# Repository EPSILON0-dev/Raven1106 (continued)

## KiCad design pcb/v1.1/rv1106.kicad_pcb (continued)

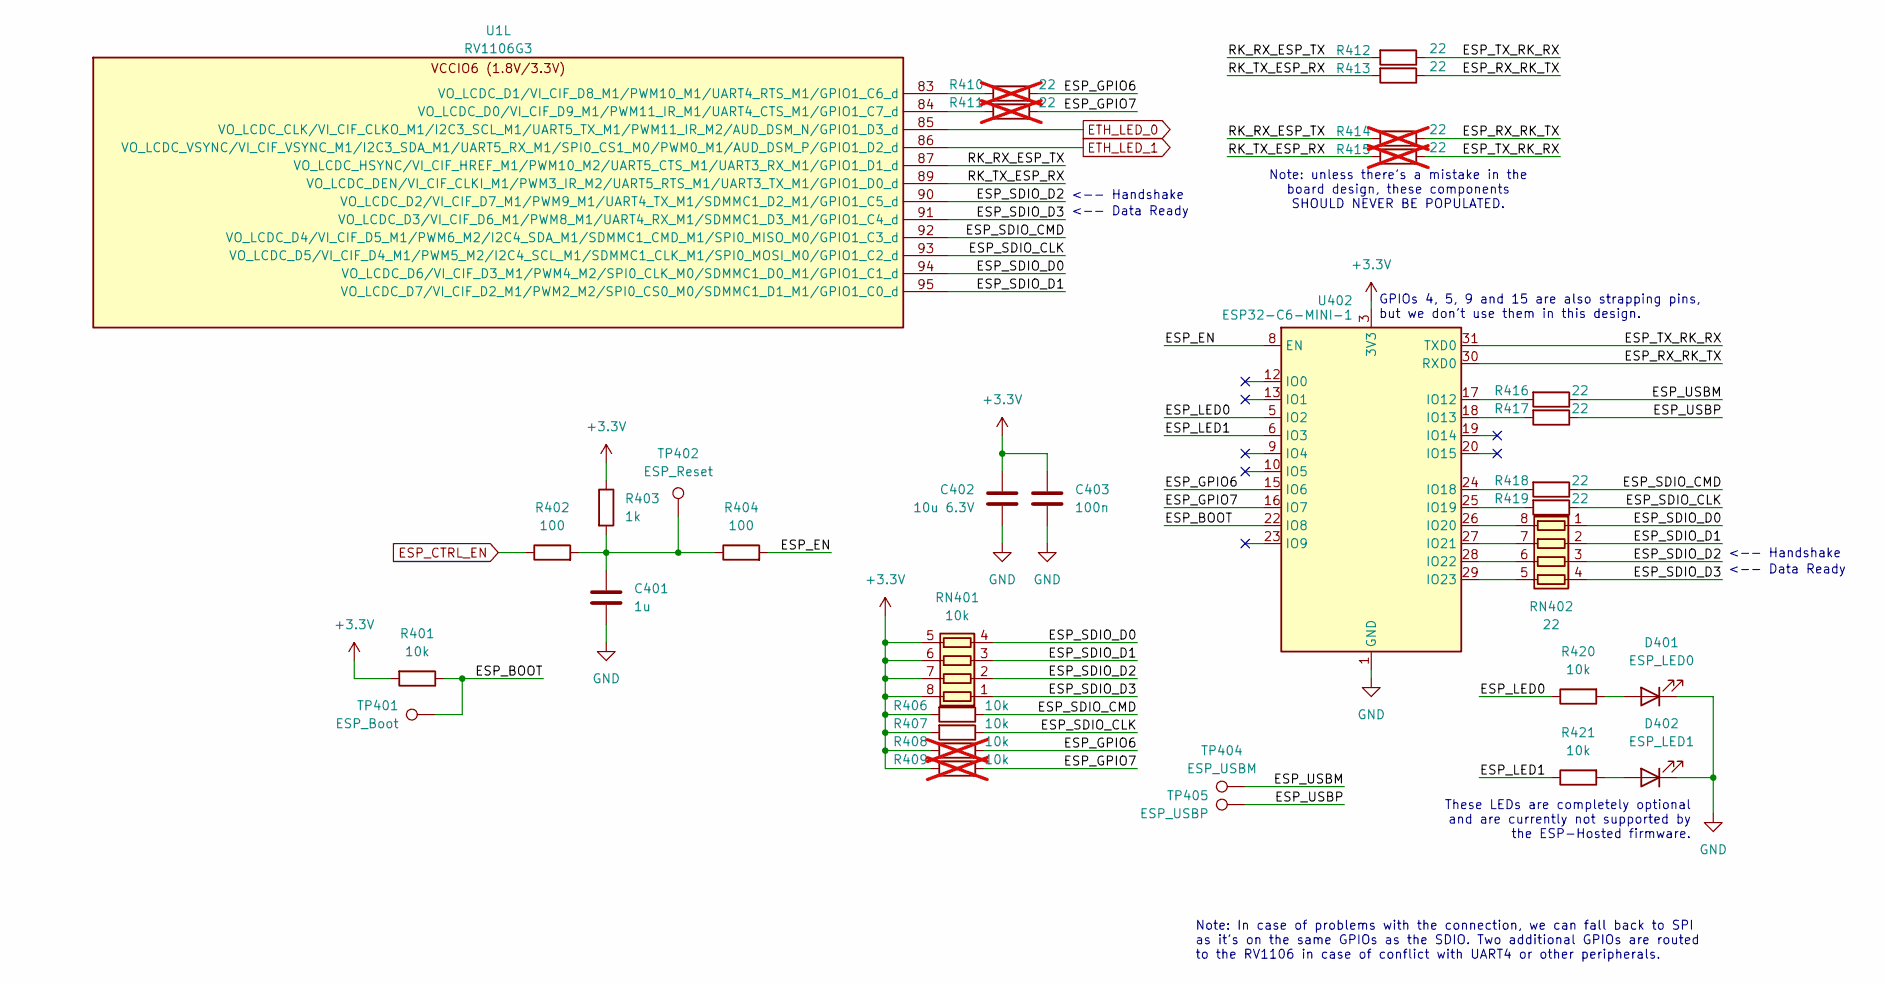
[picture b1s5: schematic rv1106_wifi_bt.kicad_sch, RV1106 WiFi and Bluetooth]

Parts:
C401: 1u; C_0402_1005Metric; LCSC C380293
C402: 10u 6.3V; C_0603_1608Metric; LCSC C1691
C403: 100n; C_0402_1005Metric; LCSC C3839219
D401: ESP_LED0; LED_0603_1608Metric
D402: ESP_LED1; LED_0603_1608Metric
R401, R406, R407, R420, R421: 10k; R_0402_1005Metric; LCSC C54531014
R402, R404: 100; R_0402_1005Metric; LCSC C54920716
R403: 1k; R_0402_1005Metric; LCSC C54531013
R408, R409: 10k; R_0402_1005Metric; not fitted
R410, R411, R414, R415: 22; R_0402_1005Metric; not fitted
R412, R413, R416, R417, R418, R419: 22; R_0402_1005Metric; LCSC C2929994
RN401: 10k; R_Array_Convex_4x0402; LCSC C168183
RN402: 22; R_Array_Convex_4x0402; LCSC C168184
TP401: ESP_Boot; TestPoint_Pad_D1.5mm
TP402: ESP_Reset; TestPoint_Pad_D1.5mm
TP404: ESP_USBM; TestPoint_Pad_D2.0mm
TP405: ESP_USBP; TestPoint_Pad_D2.0mm
U1: RV1106G3; Rockchip_QFN-128-1EP_12.3x12.3mm_P0.35mm_EP7x7mm
U402: ESP32-C6-MINI-1

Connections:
+3.3V: C402.1, C403.1, R401.2, R403.1, R406.2, R407.2, R408.2, R409.2, RN401.5 (R4.2), RN401.6 (R3.2), RN401.7 (R2.2), RN401.8 (R1.2), U402.3 (3V3); also elsewhere on the board
/WiFi and Bluetooth/ESP_BOOT: R401.1, TP401.1 (1_1), U402.22 (IO8)
/WiFi and Bluetooth/ESP_EN: R404.2, U402.8 (EN)
/WiFi and Bluetooth/ESP_GPIO6: R408.1, R410.1, U402.15 (IO6)
/WiFi and Bluetooth/ESP_GPIO7: R409.1, R411.1, U402.16 (IO7)
/WiFi and Bluetooth/ESP_LED0: R420.1, U402.5 (IO2)
/WiFi and Bluetooth/ESP_LED1: R421.1, U402.6 (IO3)
/WiFi and Bluetooth/ESP_RX_RK_TX: R413.1, R414.1, U402.30 (RXD0)
/WiFi and Bluetooth/ESP_SDIO_CLK: R407.1, R419.1, U1.93 (VO_LCDC_D5/VI_CIF_D4_M1/PWM5_M2/I2C4_SC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)
/WiFi and Bluetooth/ESP_SDIO_CMD: R406.1, R418.1, U1.92 (VO_LCDC_D4/VI_CIF_D5_M1/PWM6_M2/I2C4_SD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)
/WiFi and Bluetooth/ESP_SDIO_D0: RN401.4 (R4.1), RN402.1 (R1.1), U1.94 (VO_LCDC_D6/VI_CIF_D3_M1/PWM4_M2/SPI0_CL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)
/WiFi and Bluetooth/ESP_SDIO_D1: RN401.3 (R3.1), RN402.2 (R2.1), U1.95 (VO_LCDC_D7/VI_CIF_D2_M1/PWM2_M2/SPI0_CS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)
/WiFi and Bluetooth/ESP_SDIO_D2: RN401.2 (R2.1), RN402.3 (R3.1), U1.90 (VO_LCDC_D2/VI_CIF_D7_M1/PWM9_M1/UART4_T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)
/WiFi and Bluetooth/ESP_SDIO_D3: RN401.1 (R1.1), RN402.4 (R4.1), U1.91 (VO_LCDC_D3/VI_CIF_D6_M1/PWM8_M1/UART4_R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)
/WiFi and Bluetooth/ESP_TX_RK_RX: R412.1, R415.1, U402.31 (TXD0)
/WiFi and Bluetooth/ESP_USBM: R416.1, TP404.1 (1_1)
/WiFi and Bluetooth/ESP_USBP: R417.1, TP405.1 (1_1)
/WiFi and Bluetooth/RK_RX_ESP_TX: R412.2, R414.2, U1.87 (VO_LCDC_HSYNC/VI_CIF_HREF_M1/PWM10_M2/U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)
/WiFi and Bluetooth/RK_TX_ESP_RX: R413.2, R415.2, U1.89 (VO_LCDC_DEN/VI_CIF_CLKI_M1/PWM3_IR_M2/U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)
ESP_CTRL_EN: R402.1; also elsewhere on the board
ETH_LED_0: U1.85 (VO_LCDC_CLK/VI_CIF_CLKO_M1/I2C3_SCL_M1/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); also elsewhere on the board
ETH_LED_1: U1.86 (VO_LCDC_VSYNC/VI_CIF_VSYNC_M1/I2C3_SDA_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); also elsewhere on the board
GND: C401.2, C402.2, C403.2, D401.1 (K), D402.1 (K), U402.1 (GND), U402.2 (GND), U402.11 (GND), U402.14 (GND), U402.36 (GND), U402.37 (GND), U402.38 (GND), U402.39 (GND), U402.40 (GND), U402.41 (GND), U402.42 (GND), U402.43 (GND), U402.44 (GND), U402.45 (GND), U402.46 (GND), U402.47 (GND), U402.48 (GND), U402.49 (GND), U402.50 (GND), U402.51 (GND), U402.52 (GND), U402.53 (GND); also elsewhere on the board
unnamed: C401.1, R402.2, R403.2, R404.1, TP402.1 (1_1)
unnamed: D401.2 (A), R420.2
unnamed: D402.2 (A), R421.2
unnamed: RN402.8 (R1.2), U402.26 (IO20)
unnamed: RN402.7 (R2.2), U402.27 (IO21)
unnamed: RN402.6 (R3.2), U402.28 (IO22)
unnamed: RN402.5 (R4.2), U402.29 (IO23)
unnamed: R411.2, U1.84 (VO_LCDC_D0/VI_CIF_D9_M1/PWM11_IR_M1/UAR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)
unnamed: R410.2, U1.83 (VO_LCDC_D1/VI_CIF_D8_M1/PWM10_M1/UART4_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)
unnamed: R416.2, U402.17 (IO12)
unnamed: R417.2, U402.18 (IO13)
unnamed: R418.2, U402.24 (IO18)
unnamed: R419.2, U402.25 (IO19)

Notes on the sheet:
These LEDs are completely optional and are currently not supported by the ESP-Hosted firmware.
<-- Data Ready
<-- Handshake
Note: In case of problems with the connection, we can fall back to SPI as it's on the same GPIOs as the SDIO. Two additional GPIOs are routed to the RV1106 in case of conflict with UART4 or other peripherals.
Note: unless there's a mistake in the board design, these components SHOULD NEVER BE POPULATED.
GPIOs 4, 5, 9 and 15 are also strapping pins, but we don't use them in this design.

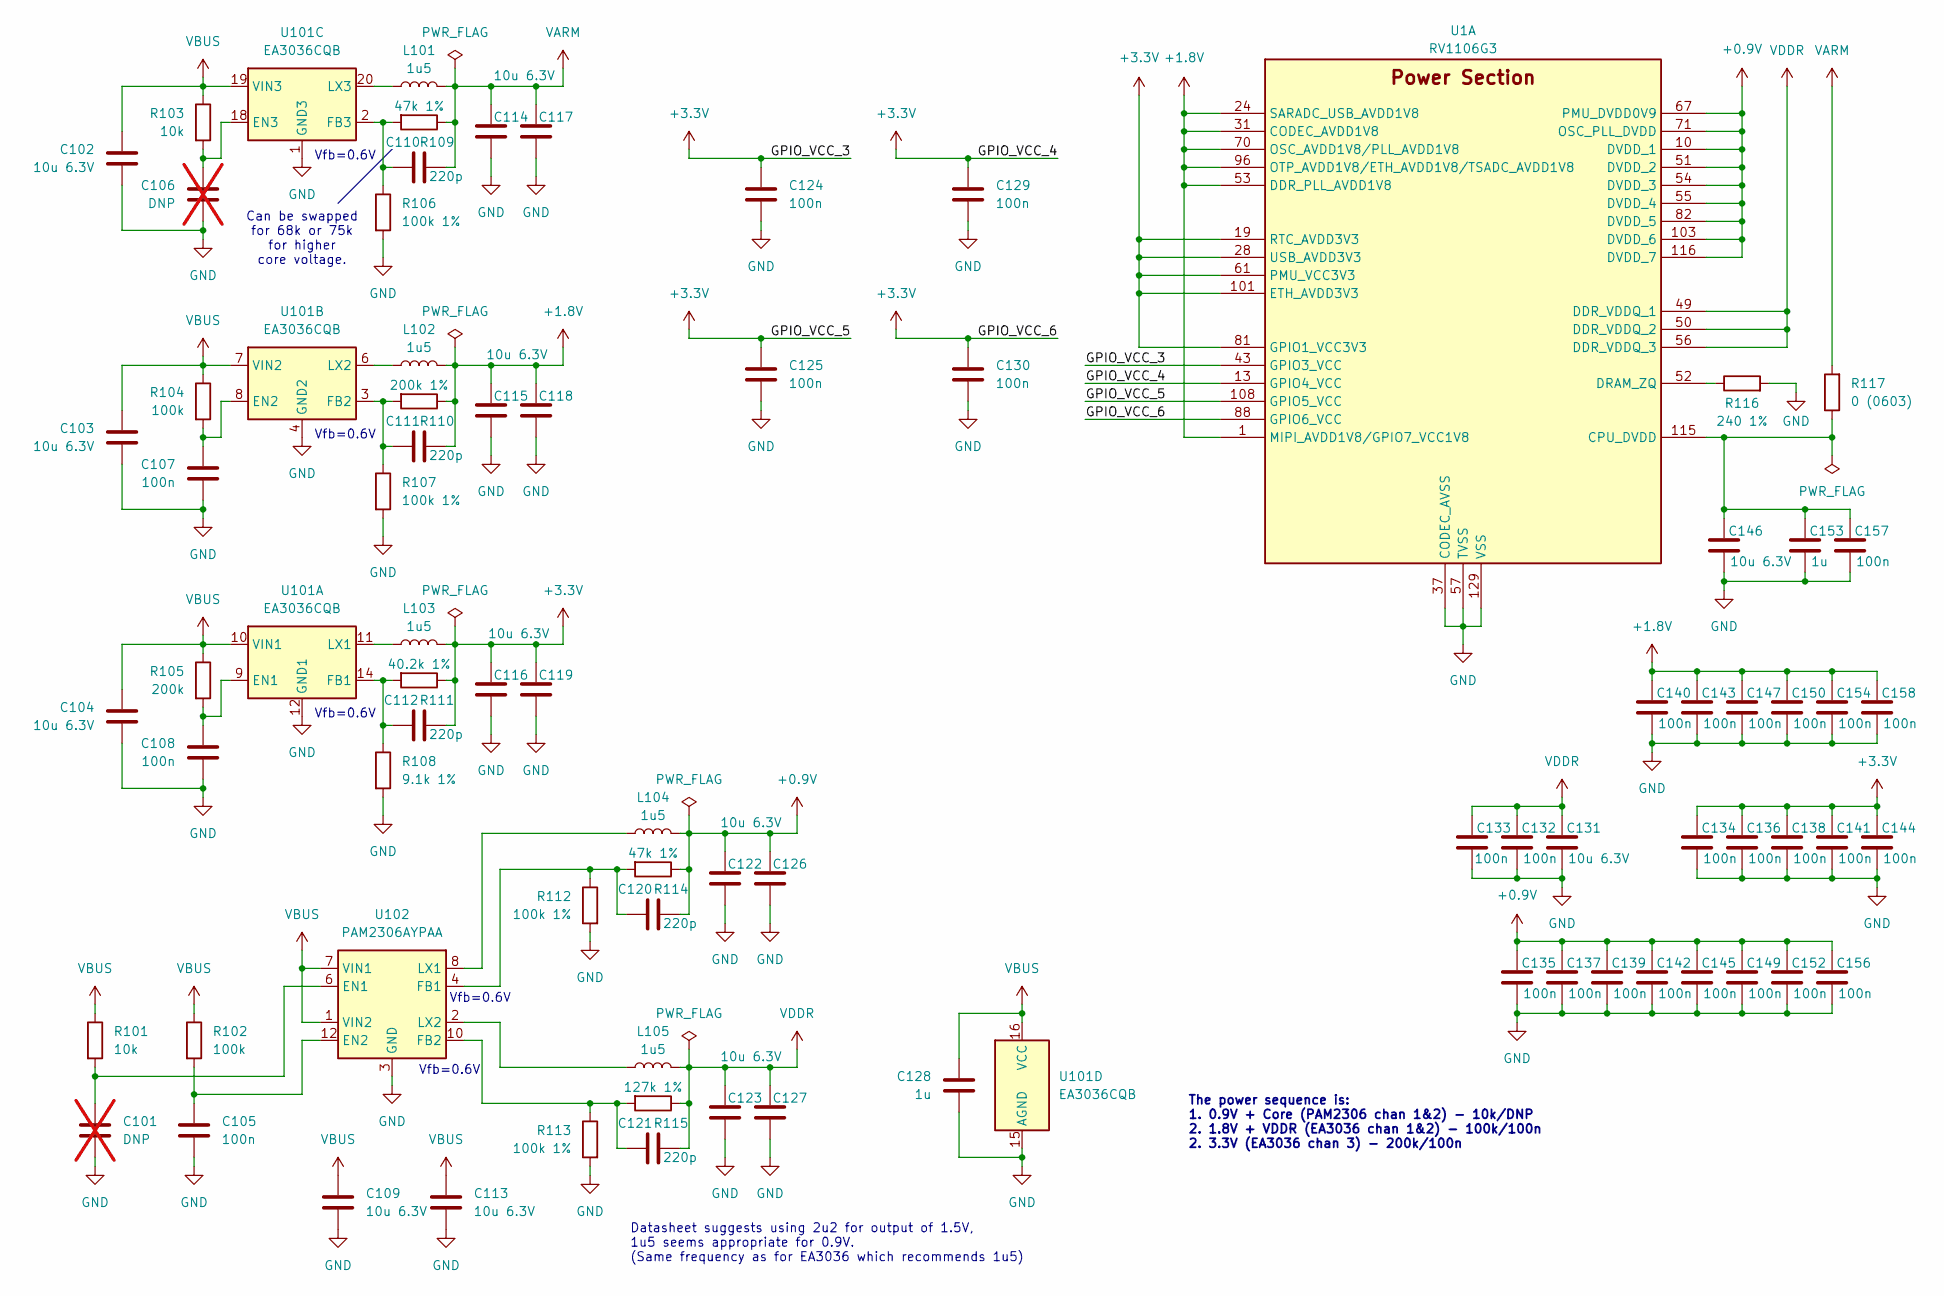
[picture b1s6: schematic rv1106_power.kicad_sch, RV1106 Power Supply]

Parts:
C101, C106: DNP; C_0402_1005Metric; not fitted
C102, C103, C104, C109, C113, C114, C115, C116, C117, C118, C119, C122, C123, C126, C127, C131, C146: 10u 6.3V; C_0603_1608Metric; LCSC C1691
C105, C107, C108, C124, C125, C129, C130, C132, C133, C134, C135, C136, C137, C138, C139, C140, C141, C142, C143, C144, C145, C147, C149, C150, C152, C154, C156, C157, C158: 100n; C_0402_1005Metric; LCSC C3839219
C110, C111, C112, C120, C121: 220p; C_0402_1005Metric; LCSC C50323515
C128, C153: 1u; C_0402_1005Metric; LCSC C380293
L101, L102, L103, L104, L105: 1u5; L_1008_2520Metric; LCSC C53514831
R101, R103: 10k; R_0402_1005Metric; LCSC C54531014
R102, R104: 100k; R_0402_1005Metric; LCSC C53224176
R105: 200k; R_0402_1005Metric; LCSC C54920643
R106, R107, R112, R113: 100k 1%; R_0402_1005Metric; LCSC C53224176
R108: 9.1k 1%; R_0402_1005Metric; LCSC C54920711
R109, R114: 47k 1%; R_0402_1005Metric; LCSC C18222281
R110: 200k 1%; R_0402_1005Metric; LCSC C54920643
R111: 40.2k 1%; R_0402_1005Metric; LCSC C25893
R115: 127k 1%; R_0402_1005Metric; LCSC C48391434
R116: 240 1%; R_0402_1005Metric; LCSC C2909339
R117: 0 (0603); R_0603_1608Metric; LCSC C53224183
U1: RV1106G3; Rockchip_QFN-128-1EP_12.3x12.3mm_P0.35mm_EP7x7mm
U101: EA3036CQB; QFN-20-1EP_3x3mm_P0.4mm_EP1.65x1.65mm; LCSC C570857
U102: PAM2306AYPAA; WDFN-12-1EP_3x3mm_P0.45mm_EP1.7x2.5mm; LCSC C508237

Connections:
+0.9V: C120.2, C122.2, C126.2, C135.1, C137.1, C139.1, C142.1, C145.1, C149.1, C152.1, C156.1, L104.2, R114.1, U1.10 (DVDD_1), U1.51 (DVDD_2), U1.54 (DVDD_3), U1.55 (DVDD_4), U1.67 (PMU_DVDD0V9), U1.71 (OSC_PLL_DVDD), U1.82 (DVDD_5), U1.103 (DVDD_6), U1.116 (DVDD_7)
+1.8V: C111.2, C115.2, C118.2, C140.1, C143.1, C147.1, C150.1, C154.1, C158.1, L102.2, R110.1, U1.1 (MIPI_AVDD1V8/GPIO7_VCC1V8), U1.24 (SARADC_USB_AVDD1V8), U1.31 (CODEC_AVDD1V8), U1.53 (DDR_PLL_AVDD1V8), U1.70 (OSC_AVDD1V8/PLL_AVDD1V8), U1.96 (OTP_AVDD1V8/ETH_AVDD1V8/TSADC_AVDD1V8); also elsewhere on the board
+3.3V: C112.2, C116.2, C119.2, C124.1, C125.1, C129.1, C130.1, C134.1, C136.1, C138.1, C141.1, C144.1, L103.2, R111.1, U1.13 (GPIO4_VCC), U1.19 (RTC_AVDD3V3), U1.28 (USB_AVDD3V3), U1.43 (GPIO3_VCC), U1.61 (PMU_VCC3V3), U1.81 (GPIO1_VCC3V3), U1.88 (GPIO6_VCC), U1.101 (ETH_AVDD3V3), U1.108 (GPIO5_VCC); also elsewhere on the board
GND: C101.1, C102.1, C103.1, C104.1, C105.1, C106.1, C107.1, C108.1, C109.1, C113.1, C114.1, C115.1, C116.1, C117.1, C118.1, C119.1, C122.1, C123.1, C124.2, C125.2, C126.1, C127.1, C128.1, C129.2, C130.2, C131.2, C132.2, C133.2, C134.2, C135.2, C136.2, C137.2, C138.2, C139.2, C140.2, C141.2, C142.2, C143.2, C144.2, C145.2, C146.2, C147.2, C149.2, C150.2, C152.2, C153.2, C154.2, C156.2, C157.2, C158.2, R106.2, R107.2, R108.2, R112.2, R113.2, R116.2, U1.37 (CODEC_AVSS), U1.57 (TVSS), U1.129 (VSS), U101.1 (GND3), U101.4 (GND2), U101.5 (GND2), U101.12 (GND1), U101.13 (GND1), U101.15 (AGND), U101.17 (AGND), U101.21 (AGND), U102.3 (GND), U102.9 (GND), U102.13 (GND); also elsewhere on the board
unnamed: C146.1, C153.1, C157.1, R117.1, U1.115 (CPU_DVDD)
unnamed: R116.1, U1.52 (DRAM_ZQ)
unnamed: C108.2, R105.2, U101.9 (EN1)
unnamed: C112.1, R108.1, R111.2, U101.14 (FB1)
unnamed: L103.1, U101.11 (LX1)
unnamed: C107.2, R104.2, U101.8 (EN2)
unnamed: C111.1, R107.1, R110.2, U101.3 (FB2)
unnamed: L102.1, U101.6 (LX2)
unnamed: C106.2, R103.2, U101.18 (EN3)
unnamed: C110.1, R106.1, R109.2, U101.2 (FB3)
unnamed: L101.1, U101.20 (LX3)
unnamed: C101.2, R101.2, U102.6 (EN1)
unnamed: C105.2, R102.2, U102.12 (EN2)
unnamed: C120.1, R112.1, R114.2, U102.4 (FB1)
unnamed: C121.1, R113.1, R115.2, U102.10 (FB2)
unnamed: L104.1, U102.8 (LX1)
unnamed: L105.1, U102.2 (LX2)
VARM: C110.2, C114.2, C117.2, L101.2, R109.1, R117.2
VBUS: C102.2, C103.2, C104.2, C109.2, C113.2, C128.2, R101.1, R102.1, R103.1, R104.1, R105.1, U101.7 (VIN2), U101.10 (VIN1), U101.16 (VCC), U101.19 (VIN3), U102.1 (VIN2), U102.7 (VIN1); also elsewhere on the board
VDDR: C121.2, C123.2, C127.2, C131.1, C132.1, C133.1, L105.2, R115.1, U1.49 (DDR_VDDQ_1), U1.50 (DDR_VDDQ_2), U1.56 (DDR_VDDQ_3)

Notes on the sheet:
Vfb=0.6V
Can be swapped for 68k or 75k for higher core voltage.
The power sequence is: 1. 0.9V + Core (PAM2306 chan 1&2) - 10k/DNP 2. 1.8V + VDDR (EA3036 chan 1&2) - 100k/100n 2. 3.3V (EA3036 chan 3) - 200k/100n
Datasheet suggests using 2u2 for output of 1.5V, 1u5 seems appropriate for 0.9V. (Same frequency as for EA3036 which recommends 1u5)

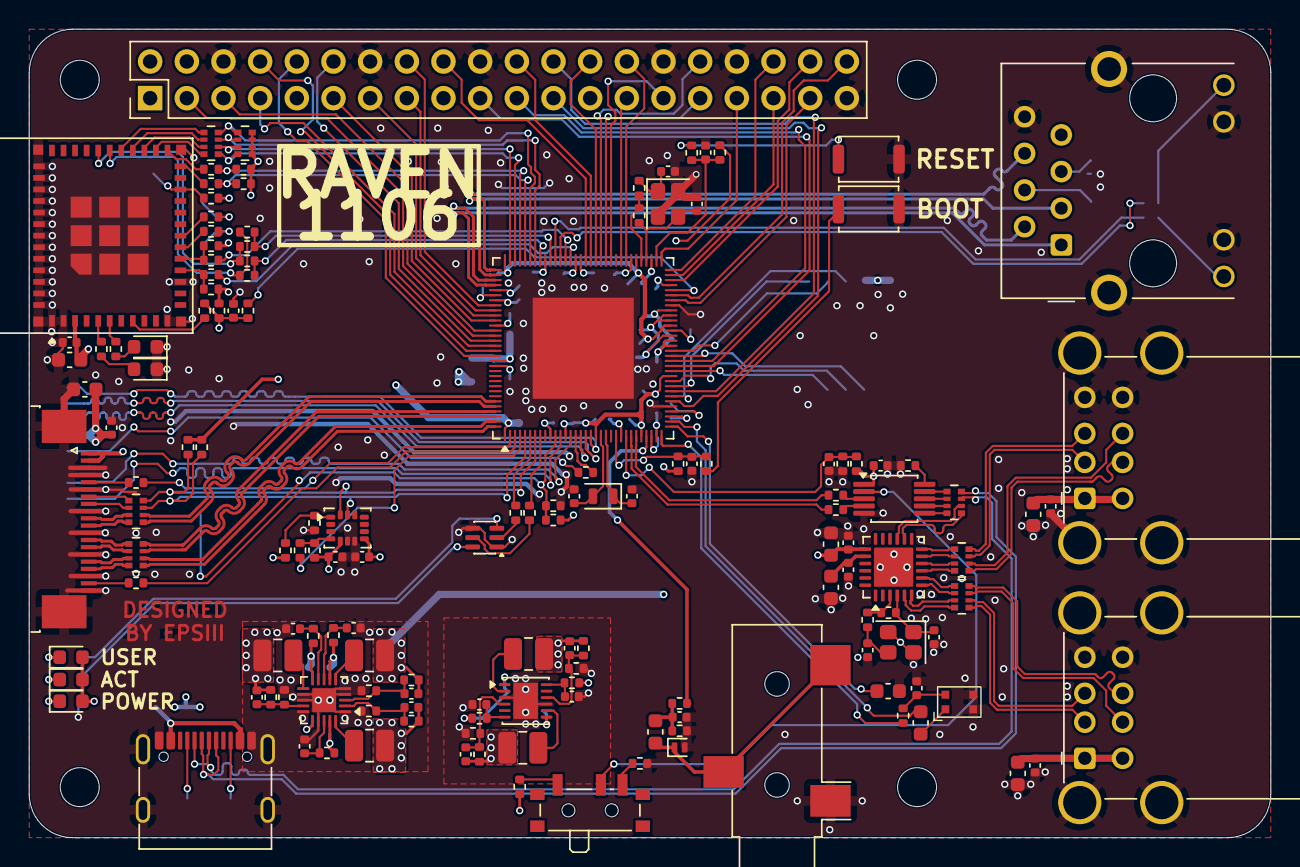
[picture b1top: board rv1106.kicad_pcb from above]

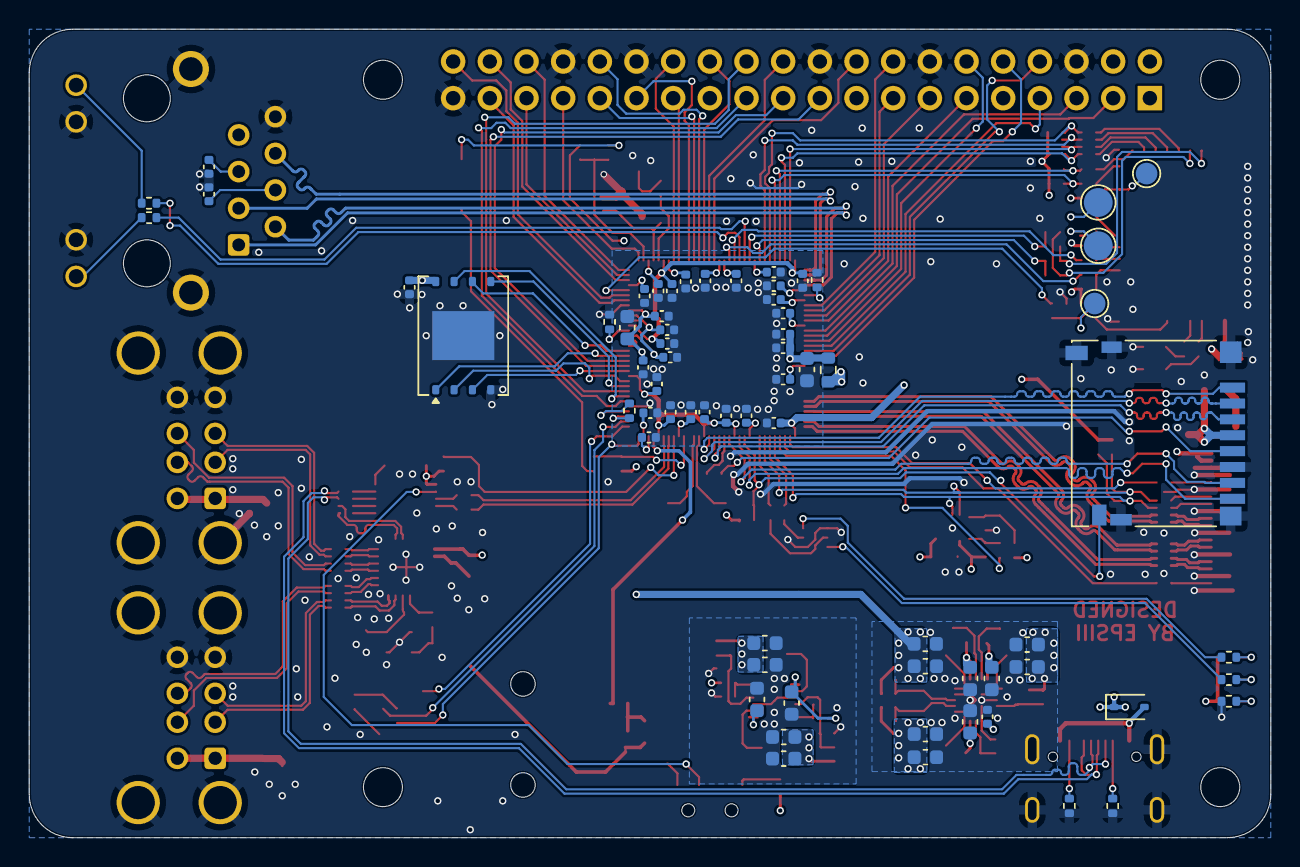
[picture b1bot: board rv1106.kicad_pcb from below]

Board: 4 copper layers, 86.0 x 56.0 mm, 217 parts (67 on the bottom side), 201 nets.
